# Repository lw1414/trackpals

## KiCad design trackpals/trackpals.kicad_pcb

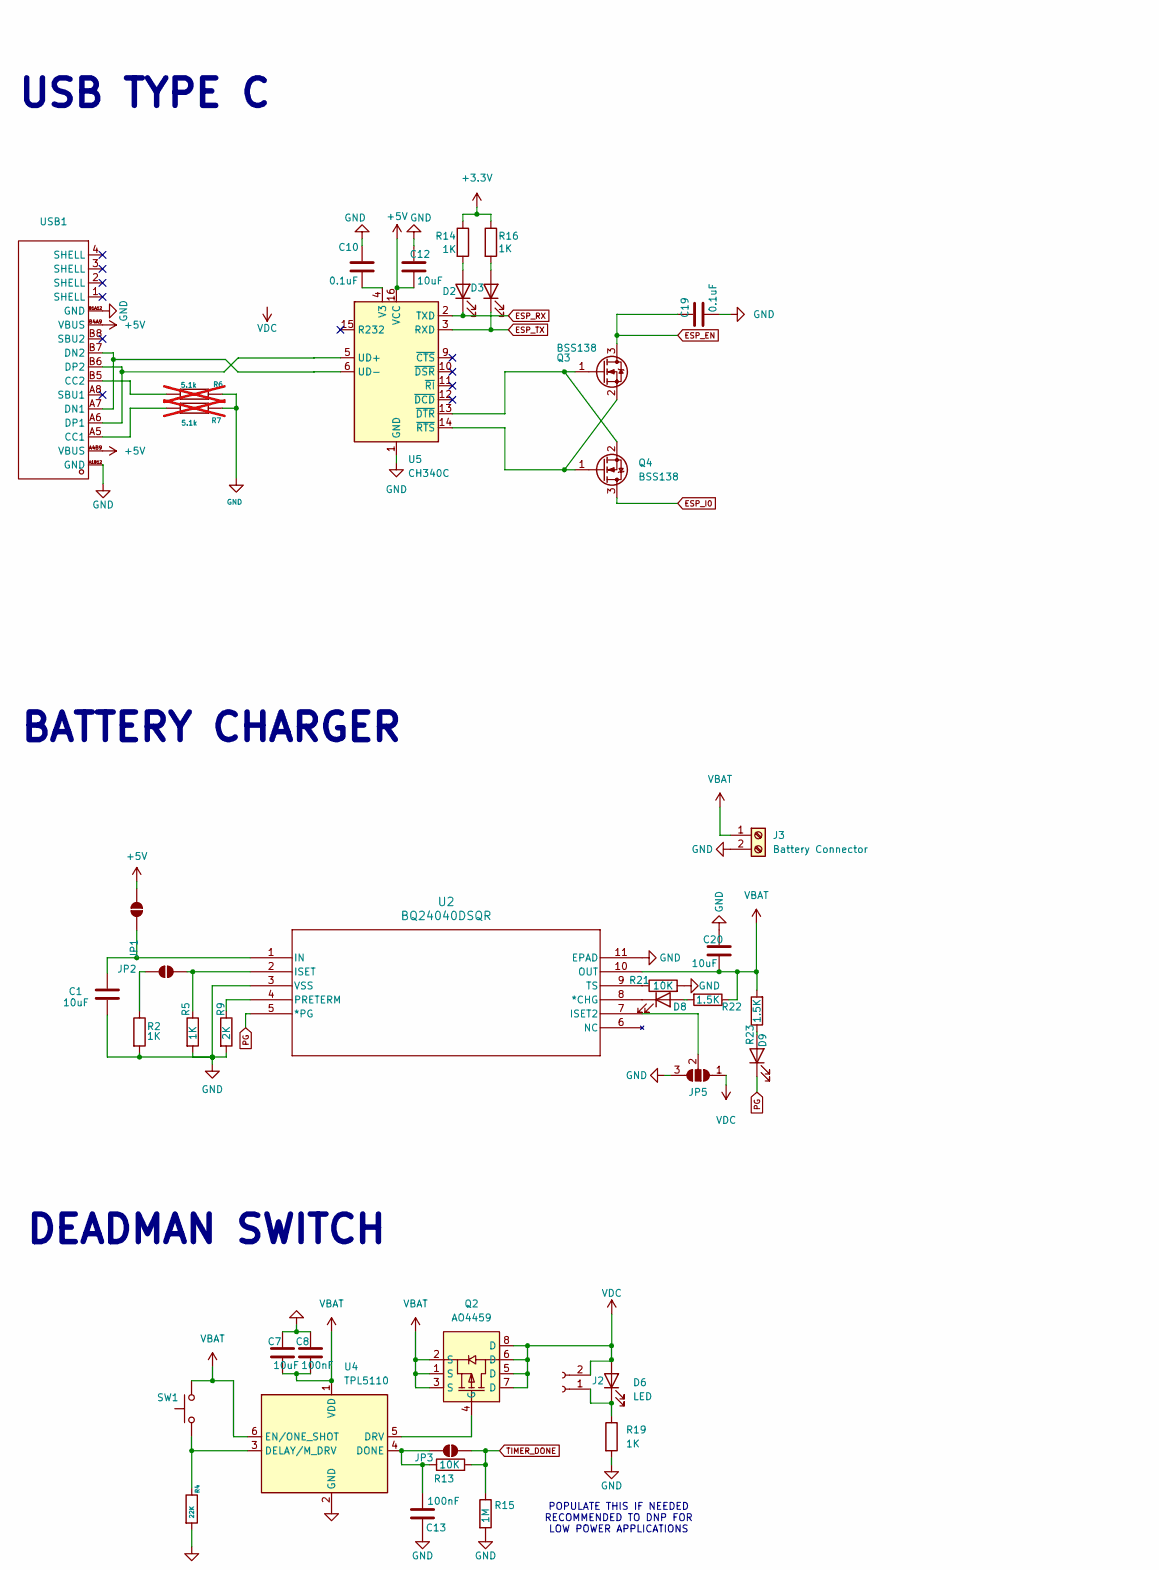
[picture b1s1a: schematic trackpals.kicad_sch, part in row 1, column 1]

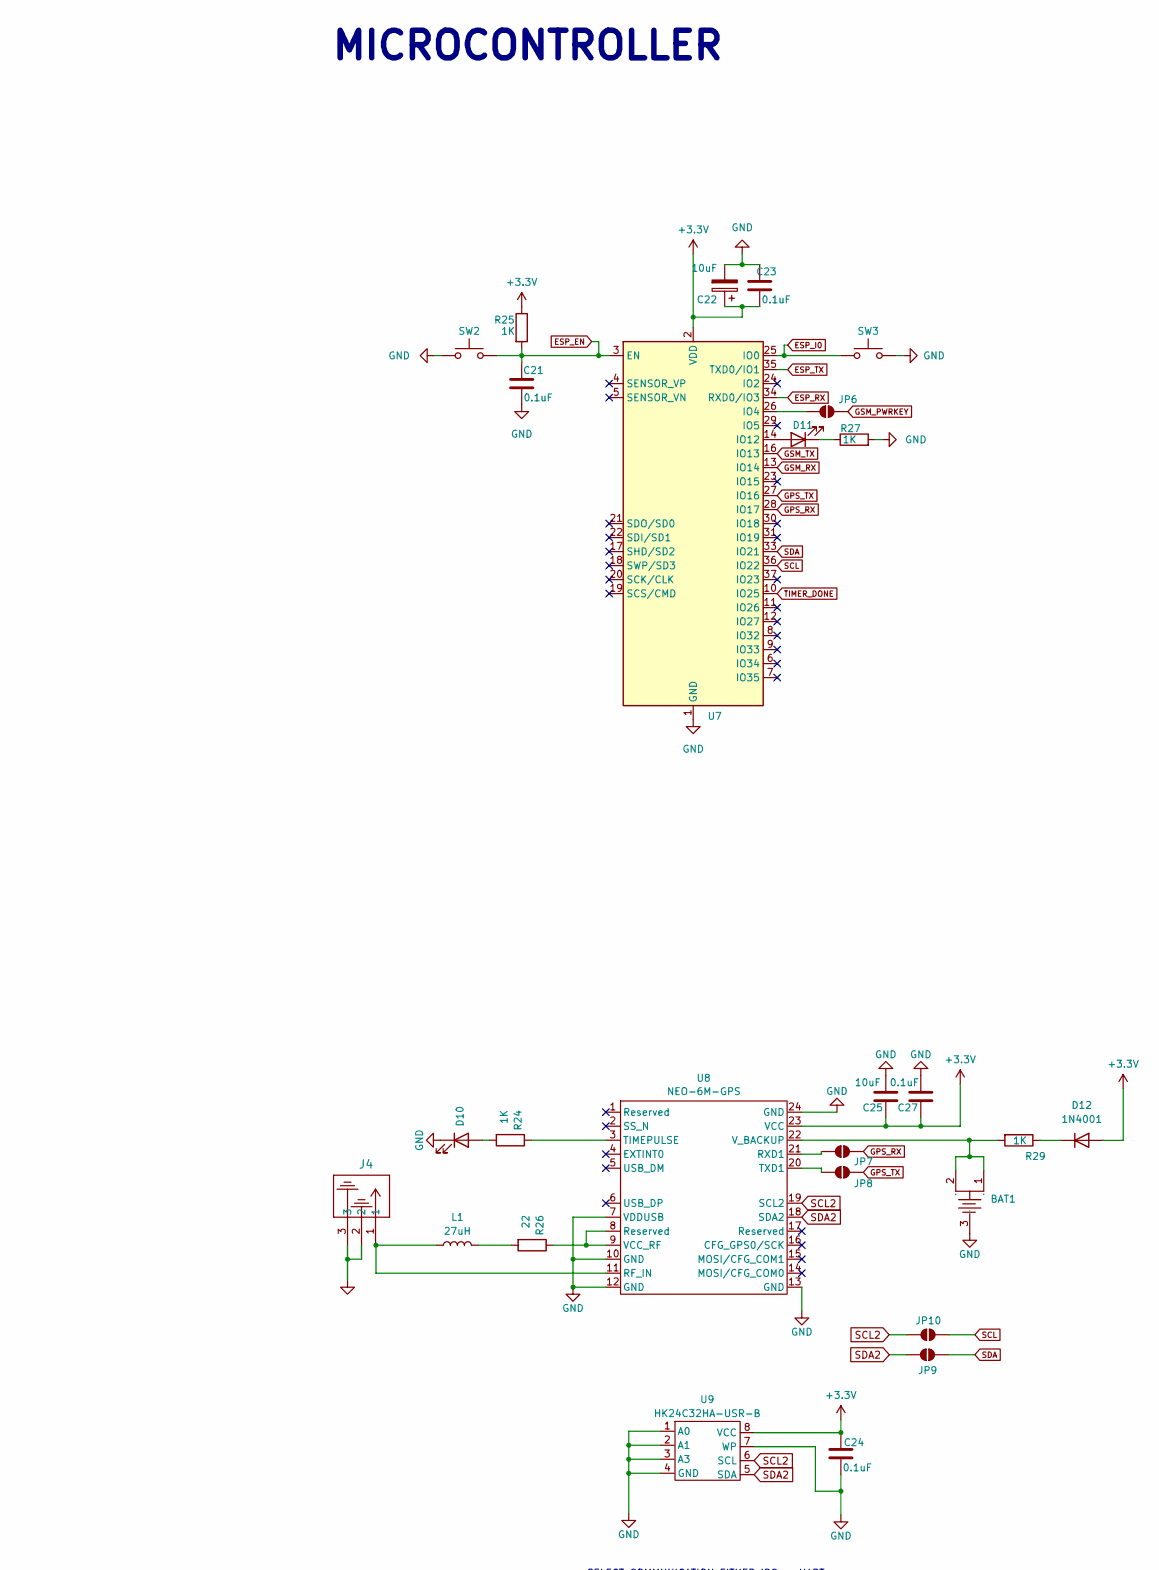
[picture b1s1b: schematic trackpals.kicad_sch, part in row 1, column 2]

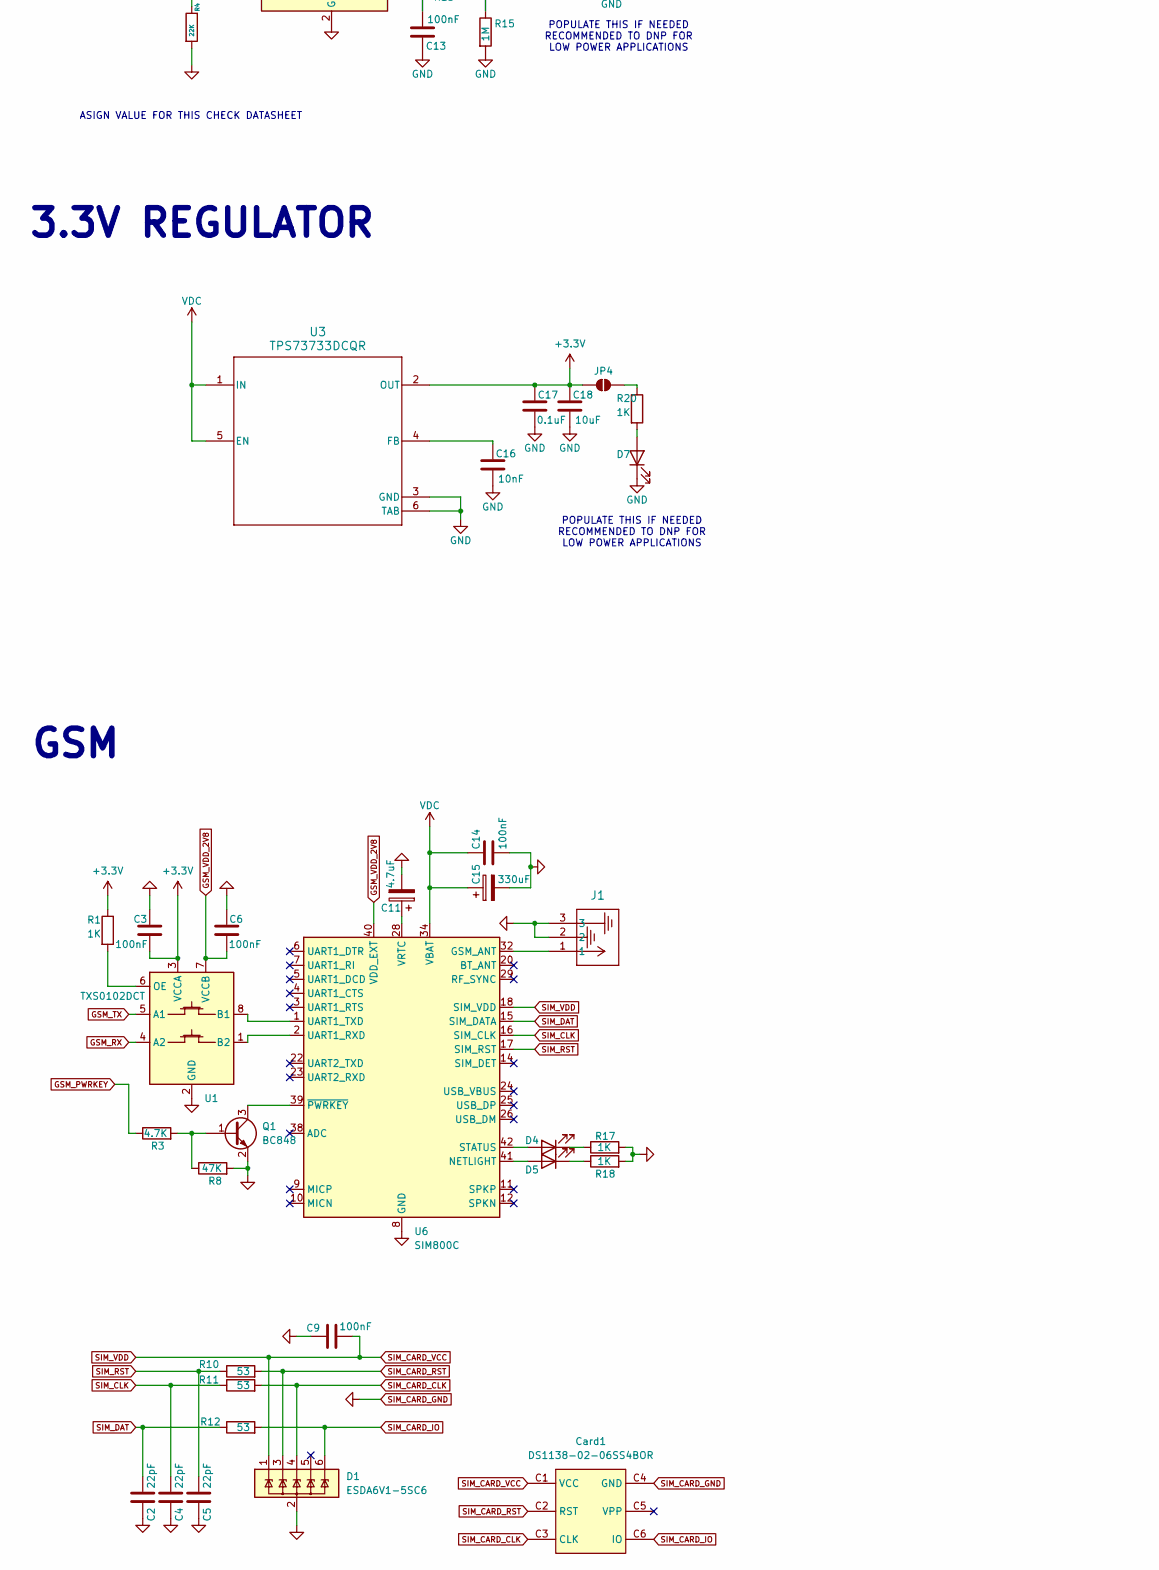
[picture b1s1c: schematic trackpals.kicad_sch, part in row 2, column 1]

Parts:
BAT1: BAT-SMD_CR1202; Manufacturer Part 3000; LCSC Part Name 3000
C1, C7, C12, C18, C20, C22, C25: 10uF; C_0805_2012Metric_Pad1.18x1.45mm_HandSolder; LCSC C15850
C2, C4, C5: 22pF; C_0603_1608Metric_Pad1.08x0.95mm_HandSolder; LCSC C105620
C3, C6, C9, C14: 100nF; C_0603_1608Metric_Pad1.08x0.95mm_HandSolder; LCSC C14663
C8: 100nF; C_0805_2012Metric_Pad1.18x1.45mm_HandSolder
C10, C17, C19, C21, C23, C24, C27: 0.1uF; C_0805_2012Metric_Pad1.18x1.45mm_HandSolder; LCSC C49678
C11: 4.7uF; CP_EIA-3528-12_Kemet-T_HandSolder; LCSC C7206
C13: 100nF; C_0805_2012Metric_Pad1.18x1.45mm_HandSolder; LCSC C60474
C15: 330uF; CP_EIA-7343-31_Kemet-D_HandSolder; LCSC C7226
C16: 10nF; C_0402_1005Metric; LCSC C60133
Card1: DS1138-02-06SS4BOR; SIM-SMD_DS1138-02-06SS4BOR; LCSC C91413
D1: ESDA6V1-5SC6; SOT-23-6; LCSC C2827672
D2, D3, D4, D5, D6, D7, D10, D11: LED; LED_0805_2012Metric_Pad1.15x1.40mm_HandSolder; LCSC C2297
D8: CHG; LED_0805_2012Metric_Pad1.15x1.40mm_HandSolder; LCSC C2286
D9: PGOOD; LED_0805_2012Metric_Pad1.15x1.40mm_HandSolder; LCSC C2297
D12: 1N4001; D_SOD-123F; LCSC C2892326
J1, J4: CONUFL001-SMD-T; IPEX-SMD_3P-L2.6-W2.6-LS3.0; LCSC C5137195
J2: Conn_01x02_Socket; PinHeader_1x02_P2.54mm_Vertical
J3: Battery Connector; JST_XH_B2B-XH-AM_1x02_P2.50mm_Vertical
JP1, JP2, JP4, JP7, JP8, JP9, JP10: SolderJumper_2_Open; SolderJumper-2_P1.3mm_Open_RoundedPad1.0x1.5mm
JP3, JP6: SolderJumper_2_Open; SolderJumper-2_P1.3mm_Open_Pad1.0x1.5mm
JP5: SolderJumper_3_Open; SolderJumper-3_P1.3mm_Open_RoundedPad1.0x1.5mm
L1: 27uH; L_0603_1608Metric_Pad1.05x0.95mm_HandSolder; LCSC C2885873
Q1: BC848; SOT-23; LCSC C88013
Q2: AO4459; SOP-8_L5.0-W4.0-P1.27-LS6.2-BL; LCSC Part C49047
Q3, Q4: BSS138; SOT-23; LCSC C426569
R1, R2, R5, R14, R16, R17, R18, R20, R24, R25, R27, R29: 1K; R_0603_1608Metric_Pad0.98x0.95mm_HandSolder; LCSC C21190
R3: 4.7K; R_0603_1608Metric_Pad0.98x0.95mm_HandSolder; LCSC C99782
R4: 22K; R_0805_2012Metric_Pad1.20x1.40mm_HandSolder; LCSC C2907128
R6, R7: 5.1k; R_0603_1608Metric_Pad0.98x0.95mm_HandSolder; LCSC C103079; not fitted
R8: 47K; R_0805_2012Metric_Pad1.20x1.40mm_HandSolder; LCSC C17713
R9: 2K; R_0603_1608Metric_Pad0.98x0.95mm_HandSolder; LCSC C22975
R10, R11, R12: 53; R_0805_2012Metric_Pad1.20x1.40mm_HandSolder; LCSC C2907334
R13, R21: 10K; R_0603_1608Metric_Pad0.98x0.95mm_HandSolder; LCSC C25804
R15: 1M; R_0805_2012Metric_Pad1.20x1.40mm_HandSolder; LCSC C105578
R19: 1K; R_0603_1608Metric_Pad0.98x0.95mm_HandSolder
R22, R23: 1.5K; R_0603_1608Metric_Pad0.98x0.95mm_HandSolder; LCSC C22843
R26: 22; R_0603_1608Metric_Pad0.98x0.95mm_HandSolder; LCSC C21190
SW1: SW_Push; PinHeader_1x02_P2.54mm_Vertical
SW2, SW3: SW_Push; SW_Tactile_SPST_NO_Straight_CK_PTS636Sx25SMTRLFS; LCSC C2689642
U1: TXS0102DCT; SSOP-8_2.95x2.8mm_P0.65mm; LCSC C324082
U2: BQ24040DSQR; WSON-10_L2.0-W2.0-P0.40-BL-EP; LCSC C81080
U3: TPS73733DCQR; SOT-223-6_L6.5-W3.5-P1.27-BL; LCSC C31334
U4: TPL5110; SOT-23-6; LCSC C2651358
U5: CH340C; SOP-16_3.9x9.9mm_P1.27mm; LCSC C84681
U6: SIM800C; SIMCom_SIM800C; LCSC C2981431
U7: ESP32-WROOM-32; ESP32-WROOM-32U; LCSC C529577
U8: NEO-6M-GPS; XCVR_NEO-6M-GPS
U9: HK24C32HA-USR-B; TSSOP-8_4.4x3mm_P0.65mm; LCSC C33576253
USB1: USB-C-SMD_TYPE-C16PIN; Manufacturer Part TYPE-C16PIN; LCSC Part Name Type-C 母 卧贴

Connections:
+3.3V: C3.2, C17.2, C18.2, C22.1, C23.1, C24.2, C25.2, C27.2, D12.2 (A), JP4.1 (A), R1.1, R14.1, R16.1, R25.1, U1.3 (VCCA), U3.2 (OUT), U7.2 (VDD), U8.23 (VCC), U9.8 (VCC)
+5V: C12.1, JP1.1 (A), U5.16 (VCC), USB1.A4B9 (VBUS), USB1.B4A9 (VBUS)
ESP_EN: C19.2, C21.2, Q3.3 (D), R25.2, SW2.2, U7.3 (EN)
ESP_I0: Q4.3 (D), SW3.1, U7.25 (IO0)
ESP_RX: D2.1 (K), U5.2 (TXD), U7.34 (RXD0/IO3)
ESP_TX: D3.1 (K), U5.3 (RXD), U7.35 (TXD0/IO1)
GPS_RX: JP7.2 (B), U7.28 (IO17)
GPS_TX: JP8.2 (B), U7.27 (IO16)
GSM_PWRKEY: JP6.1 (A), R3.1
GSM_RX: U1.4 (A2), U7.13 (IO14)
GSM_TX: U1.5 (A1), U7.16 (IO13)
GSM_VDD_2V8: C6.2, U1.7 (VCCB), U6.40 (VDD_EXT)
unnamed: D2.2 (A), R14.2
unnamed: D3.2 (A), R16.2
unnamed: D4.2 (A), U6.42 (STATUS)
unnamed: D4.1 (K), R17.1
unnamed: D5.2 (A), U6.41 (NETLIGHT)
unnamed: D5.1 (K), R18.1
unnamed: D6.1 (K), J2.1, R19.1
unnamed: D7.2 (A), R20.2
unnamed: D8.2 (A), R22.2
unnamed: D8.1 (K), U2.8 (*CHG)
unnamed: D9.2 (A), R23.1
unnamed: D10.2 (A), R24.2
unnamed: D11.2 (A), U7.14 (IO12)
unnamed: D11.1 (K), R27.1
unnamed: D12.1 (K), R29.1
unnamed: C1.1, JP1.2 (B), U2.1 (IN)
unnamed: JP2.1 (A), R5.1, U2.2 (ISET)
unnamed: JP2.2 (B), R2.1
unnamed: C13.1, JP3.1 (A), R13.1, U4.4 (DONE)
unnamed: JP4.2 (B), R20.1
unnamed: JP5.2 (C), U2.7 (ISET2)
unnamed: JP6.2 (B), U7.26 (IO4)
unnamed: JP7.1 (A), U8.21 (RXD1)
unnamed: JP8.1 (A), U8.20 (TXD1)
unnamed: L1.2, R26.2
unnamed: Q1.1 (B), R3.2, R8.1
unnamed: Q1.3 (C), U6.39 (~PWRKEY)
unnamed: Q2.4 (G), U4.5 (DRV)
unnamed: Q3.1 (G), Q4.2 (S), U5.13 (~DTR)
unnamed: Q3.2 (S), Q4.1 (G), U5.14 (~RTS)
unnamed: U1.8 (B1), U6.1 (UART1_TXD)
unnamed: U1.1 (B2), U6.2 (UART1_RXD)
unnamed: R1.2, U1.6 (OE)
unnamed: R9.1, U2.4 (PRETERM)
unnamed: R21.1, U2.9 (TS)
unnamed: C16.2, U3.4 (FB)
unnamed: R4.1, SW1.1, U4.3 (DELAY/M_DRV)
unnamed: U5.5 (UD+), USB1.A6 (DP1), USB1.B6 (DP2)
unnamed: U5.6 (UD-), USB1.A7 (DN1), USB1.B7 (DN2)
unnamed: C10.1, U5.4 (V3)
unnamed: J1.1, U6.32 (GSM_ANT)
unnamed: C11.1, U6.28 (VRTC)
unnamed: J4.1, L1.1, U8.11 (RF_IN)
unnamed: R24.1, U8.3 (TIMEPULSE)
unnamed: R26.1, U8.8 (Reserved), U8.9 (VCC_RF)
unnamed: BAT1.1 (+), BAT1.2 (+), R29.2, U8.22 (V_BACKUP)
unnamed: R7.1, USB1.A5 (CC1)
unnamed: R6.1, USB1.B5 (CC2)
PG: D9.1 (K), U2.5 (*PG)
SCL: JP10.2 (B), U7.36 (IO22)
SCL2: JP10.1 (A), U8.19 (SCL2), U9.6 (SCL)
SDA: JP9.2 (B), U7.33 (IO21)
SDA2: JP9.1 (A), U8.18 (SDA2), U9.5 (SDA)
SIM_CARD_CLK: Card1.C3 (CLK), D1.4 (IO3), R11.2
SIM_CARD_GND: BAT1.3 (-), C1.2, C2.1, C3.1, C4.1, C5.1, C6.1, C7.1, C8.1, C9.1, C10.2, C11.2, C12.2, C13.2, C14.2, C15.2, C16.1, C17.1, C18.1, C19.1, C20.1, C21.1, C22.2, C23.2, C24.1, C25.1, C27.1, Card1.C4 (GND), D1.2 (GND), D7.1 (K), D10.1 (K), J1.2, J1.3, J3.2, J4.2, J4.3, JP5.3 (B), Q1.2 (E), R2.2, R4.2, R5.2, R6.2, R7.2, R8.2, R9.2, R15.2, R17.2, R18.2, R19.2, R21.2, R27.2, SW2.1, SW3.2, U1.2 (GND), U2.3 (VSS), U2.11 (EPAD), U3.3 (GND), U3.6 (TAB), U4.2 (GND), U5.1 (GND), U6.8 (GND), U6.13 (GND), U6.19 (GND), U6.21 (GND), U6.27 (GND), U6.30 (GND), U6.31 (GND), U6.33 (GND), U6.36 (GND), U6.37 (GND), U7.1 (GND), U7.15 (GND), U7.38 (GND), U7.39 (GND), U8.7 (VDDUSB), U8.10 (GND), U8.12 (GND), U8.13 (GND), U8.24 (GND), U9.1 (A0), U9.2 (A1), U9.3 (A3), U9.4 (GND), U9.7 (WP), USB1.A1B12 (GND), USB1.B1A12 (GND)
SIM_CARD_IO: Card1.C6 (IO), D1.6 (IO5), R12.2
SIM_CARD_RST: Card1.C2 (RST), D1.3 (IO2), R10.2
SIM_CARD_VCC: C9.2, Card1.C1 (VCC), D1.1 (IO1), U6.18 (SIM_VDD)
SIM_CLK: C4.2, R11.1, U6.16 (SIM_CLK)
SIM_DAT: C2.2, R12.1, U6.15 (SIM_DATA)
SIM_RST: C5.2, R10.1, U6.17 (SIM_RST)
TIMER_DONE: JP3.2 (B), R13.2, R15.1, U7.10 (IO25)
VBAT: C7.2, C8.2, C20.2, J3.1, Q2.1 (S), Q2.2 (S), Q2.3 (S), R22.1, R23.2, SW1.2, U2.10 (OUT), U4.1 (VDD), U4.6 (EN/ONE_SHOT)
VDC: C14.1, C15.1, D6.2 (A), J2.2, JP5.1 (A), Q2.5 (D), Q2.6 (D), Q2.7 (D), Q2.8 (D), U3.1 (IN), U3.5 (EN), U6.34 (VBAT), U6.35 (VBAT)

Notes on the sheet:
POPULATE THIS IF NEEDED RECOMMENDED TO DNP FOR LOW POWER APPLICATIONS
ASIGN VALUE FOR THIS CHECK DATASHEET
GSM
BATTERY CHARGER
3.3V REGULATOR
MICROCONTROLLER
SELECT COMMUNICATION EITHER I2C or UART
USB TYPE C
DEADMAN SWITCH

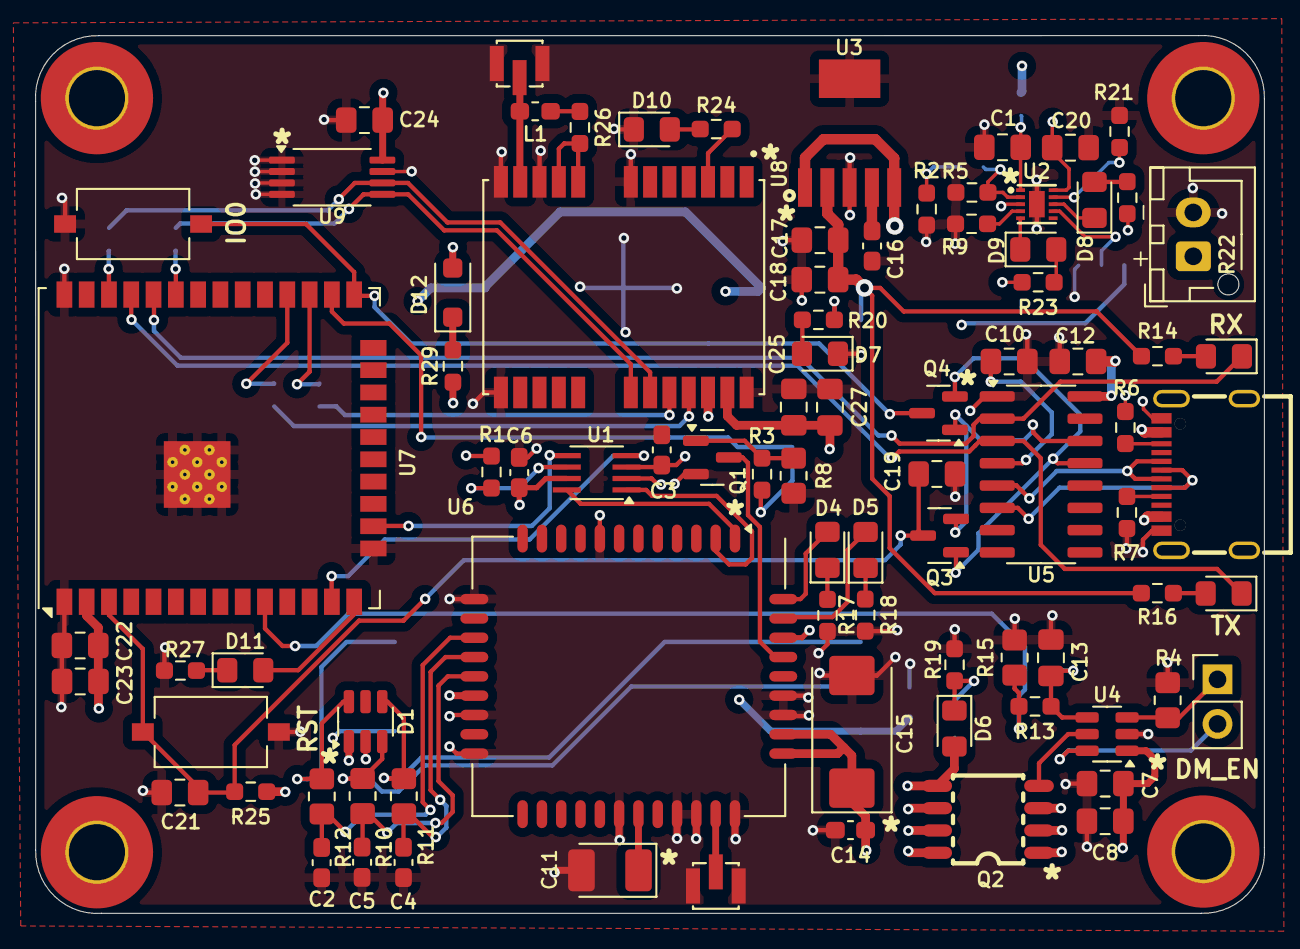
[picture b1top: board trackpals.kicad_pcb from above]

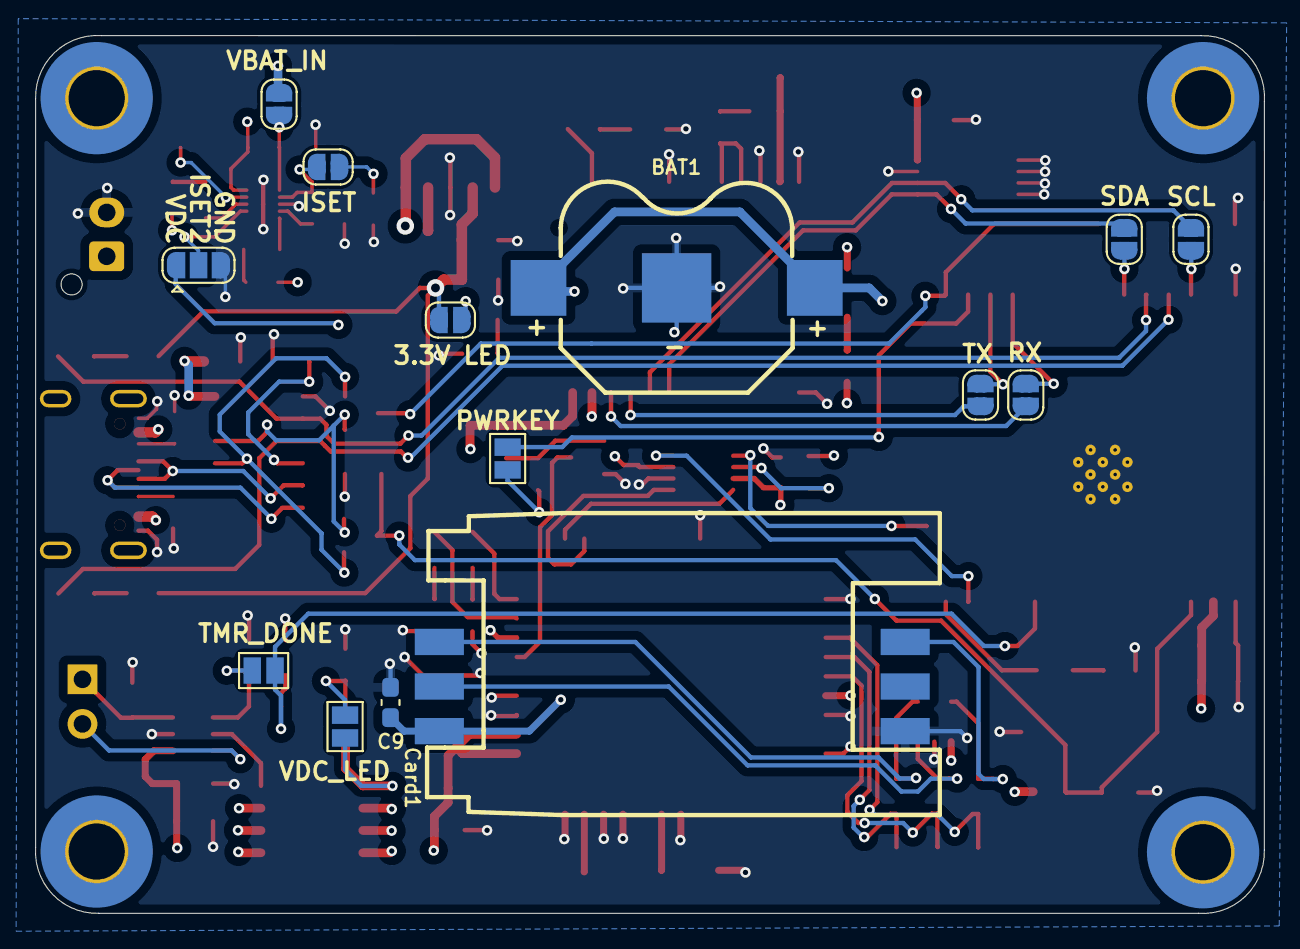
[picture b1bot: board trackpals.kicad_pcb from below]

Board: 4 copper layers, 70.0 x 50.0 mm, 104 parts (14 on the bottom side), 76 nets.

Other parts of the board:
H2, H2#2, H2#3, H2#4: MountingHole; MountingHole_3.2mm_M3_Pad_TopBottom

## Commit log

2026-02-06 scheme draft done
2026-02-08 -done placement ng pcb
2026-02-09 - DONE PCB
2026-02-10 updated tssop
